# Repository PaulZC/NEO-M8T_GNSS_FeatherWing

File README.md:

# NEO-M8T GNSS FeatherWing

A clone of the [Adafruit Ultimate GPS FeatherWing](https://www.adafruit.com/product/3133) but with the u-blox NEO-M8T replacing the GlobalTop FGPMMOPA6H. The NEO-M8T can receive signals from GPS, Galileo and GLONASS or BeiDou concurrently and supports both SBAS and QZSS.
It also provides Multi-GNSS Raw Measurement (RAWX) Data which can be used for Post-Processed Kinematic (PPK) positioning.

**See [LEARN.md](https://github.com/PaulZC/NEO-M8T_GNSS_FeatherWing/blob/master/LEARN.md) for more details.**

[POST_PROCESS.md](https://github.com/PaulZC/NEO-M8T_GNSS_FeatherWing/blob/master/POST_PROCESS.md) contains results of a first time successful attempt at post-processed kinematic positioning using [rtkexplorer's demo5 version of RTKLIB](http://rtkexplorer.com/downloads/rtklib-code/).

See [NEO-M8T_GNSS_FeatherWing.pdf](https://github.com/PaulZC/NEO-M8T_GNSS_FeatherWing/blob/master/NEO-M8T_GNSS_FeatherWing.pdf) for the schematic, layout and Bill Of Materials.

The [Eagle](https://github.com/PaulZC/NEO-M8T_GNSS_FeatherWing/tree/master/Eagle) directory contains the schematic and pcb design files.

The [Arduino](https://github.com/PaulZC/NEO-M8T_GNSS_FeatherWing/tree/master/Arduino) directory contains code for the [Adafruit Feather M0 Adalogger](https://www.adafruit.com/products/2796) which will log RAWX data to SD card.

Distributed under a Creative Commons Attribution, Share-Alike license.

Enjoy!

**_Paul_**

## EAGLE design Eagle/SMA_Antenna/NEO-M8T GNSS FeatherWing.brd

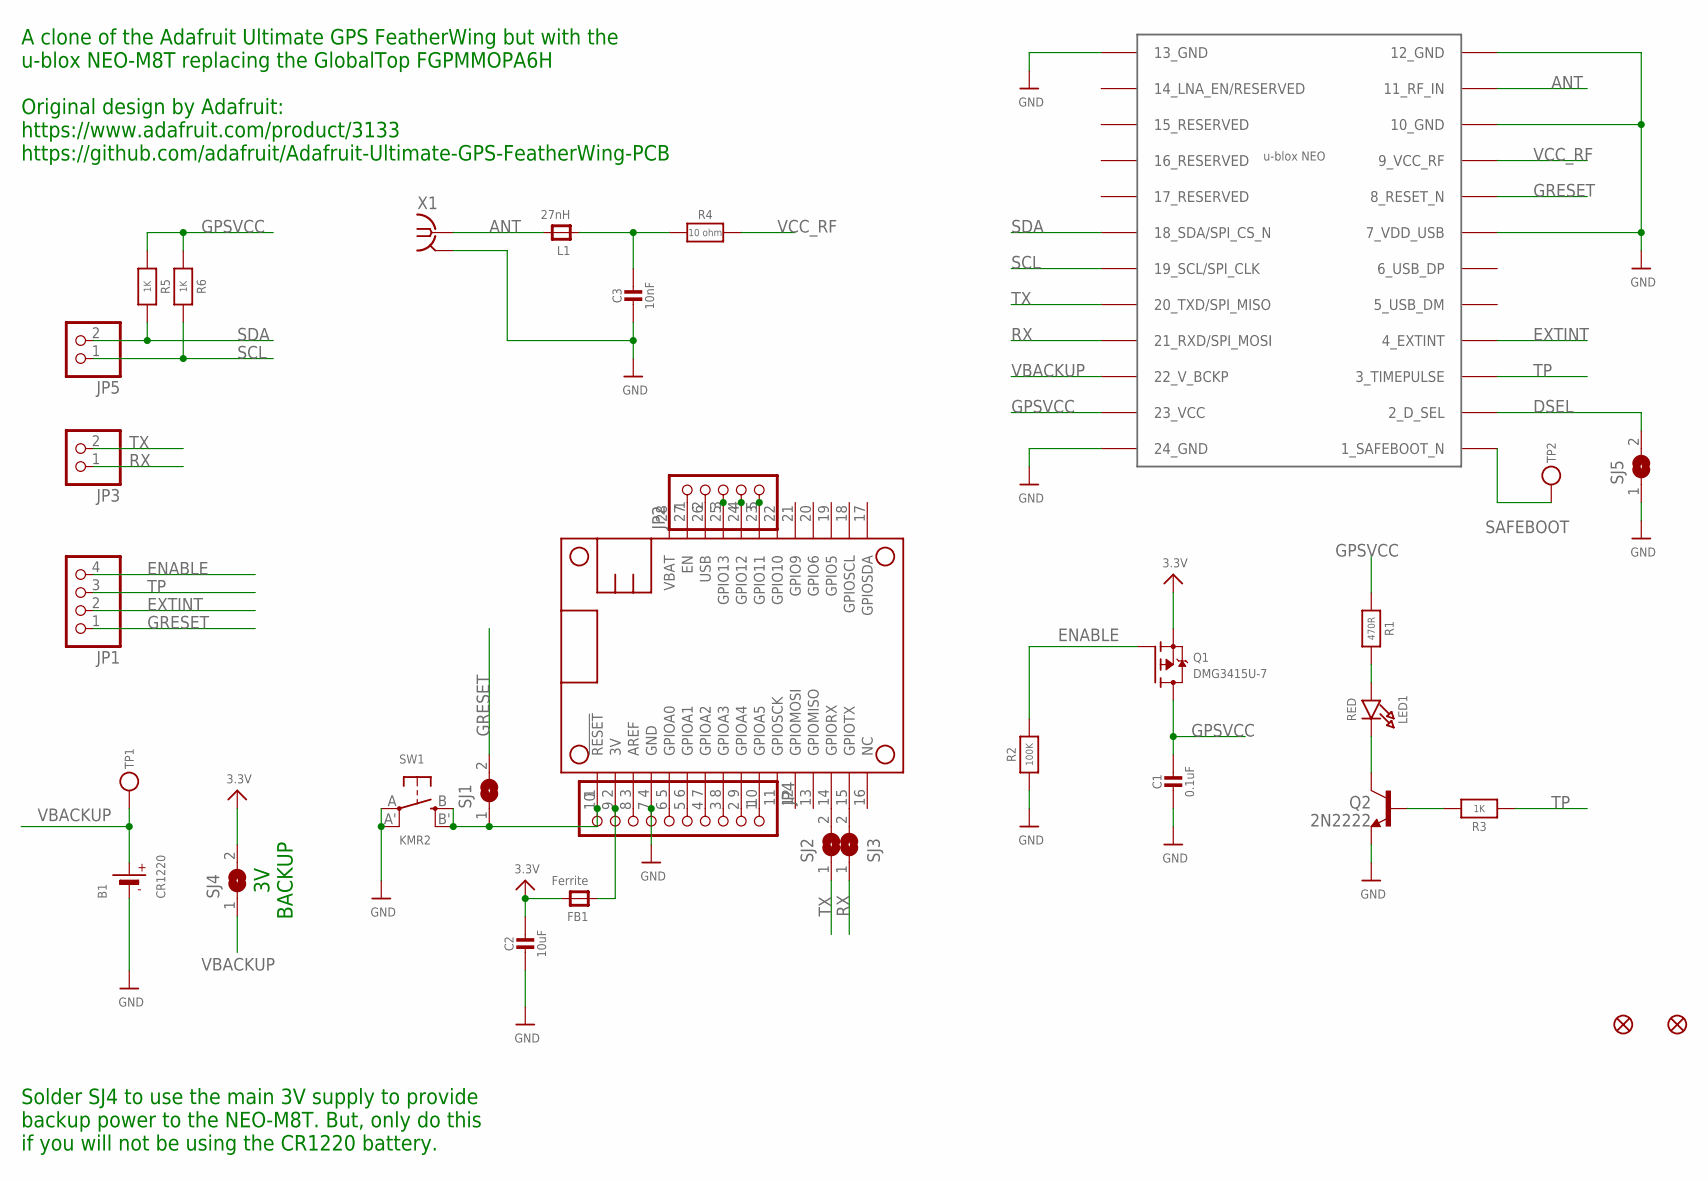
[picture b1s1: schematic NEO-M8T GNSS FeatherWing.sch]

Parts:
B1: CR1220; CR1220-2
C1: 0.1uF; 0805-NO
C2: 10uF; 0805-NO
C3: 10nF; 0805-NO
FB1: Ferrite; 0805-NO
FID1, FID2: FIDUCIAL""; FIDUCIAL_1MM
JP1: HEADER-1X4ROUND; 1X04_ROUND
JP2: HEADER-1X570MIL; 1X05_ROUND_70
JP3, JP5: HEADER-1X2ROUND; 1X02_ROUND
JP4: HEADER-1X10ROUND; 1X10_ROUND
L1: 27nH; 0805-NO
LED1: RED; CHIPLED_0805_NOOUTLINE
MS1: MICROBUILDER_FEATHERWINGSMA; MICROBUILDER_FEATHERWING_SMA
Q1: DMG3415U-7; SOT23-WIDE
Q2: 2N2222; SOT23-BEC
R1: 470R; 0603-NO
R2: 100K; 0805-NO
R3, R5, R6: 1K; 0603-NO
R4: 10 ohm; 0805-NO
SJ1, SJ4, SJ5: SOLDERJUMPER; SOLDERJUMPER_ARROW_NOPASTE
SJ2, SJ3: SOLDERJUMPERCLOSED; SOLDERJUMPER_CLOSEDWIRE
SW1: KMR2; BTN_KMR2_4.6X2.8
TP1, TP2: TESTPOINTROUND1.5MM; TESTPOINT_ROUND_1.5MM
U1: NEO-M8
X1: SMA-142-0711-821/826; J502-ND-142-0711-821/826

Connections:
3.3V: C2.1, FB1.2, Q1.2 (S), SJ4.2
3V: FB1.1, JP4.9, MS1.2 (3V)
ANT: L1.2, U1.11 (11_RF_IN), X1.1
DSEL: SJ5.2, U1.2 (2_D_SEL)
ENABLE: JP1.4, Q1.1 (G), R2.2
EXTINT: JP1.2, U1.4 (4_EXTINT)
GND: B1.-, C1.2, C2.2, C3.2, JP4.7, MS1.4 (GND), Q2.E, R2.1, SJ5.1, SW1.A, SW1.A' (P1), U1.7 (7_VDD_USB), U1.10 (10_GND), U1.12 (12_GND), U1.13 (13_GND), U1.24 (24_GND), X1.G@1 (2), X1.G@2 (2), X1.G@3 (2), X1.G@4 (2)
GPSVCC: C1.1, Q1.3 (D), R1.1, R5.1, R6.1, U1.23 (23_VCC)
GRESET: JP1.1, SJ1.2, U1.8 (8_RESET_N)
unnamed: JP2.3, MS1.25 (GPIO13)
unnamed: LED1.A, R1.2
unnamed: JP2.4, MS1.24 (GPIO12)
unnamed: C3.1, L1.1, R4.1
unnamed: JP2.5, MS1.23 (GPIO11)
unnamed: JP4.1, MS1.10 (GPIOA5)
unnamed: JP4.2, MS1.9 (GPIOA4)
unnamed: JP4.3, MS1.8 (GPIOA3)
unnamed: JP4.4, MS1.7 (GPIOA2)
unnamed: JP4.5, MS1.6 (GPIOA1)
unnamed: JP4.6, MS1.5 (GPIOA0)
unnamed: JP4.8, MS1.3 (AREF)
unnamed: JP2.1, MS1.27 (EN)
unnamed: MS1.14 (GPIORX), SJ2.2
unnamed: MS1.15 (GPIOTX), SJ3.2
unnamed: LED1.C, Q2.C
unnamed: Q2.B, R3.2
RST: JP4.10, MS1.1 (!RESET), SJ1.1, SW1.B (S), SW1.B' (S1)
RX: JP3.1, SJ3.1, U1.21 (21_RXD/SPI_MOSI)
SAFEBOOT: TP2.P$1, U1.1 (1_SAFEBOOT_N)
SCL: JP5.1, R6.2, U1.19 (19_SCL/SPI_CLK)
SDA: JP5.2, R5.2, U1.18 (18_SDA/SPI_CS_N)
TP: JP1.3, R3.1, U1.3 (3_TIMEPULSE)
TX: JP3.2, SJ2.1, U1.20 (20_TXD/SPI_MISO)
USB: JP2.2, MS1.26 (USB)
VBACKUP: B1.+, SJ4.1, TP1.P$1, U1.22 (22_V_BCKP)
VCC_RF: R4.2, U1.9 (9_VCC_RF)

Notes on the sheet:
A clone of the Adafruit Ultimate GPS FeatherWing but with the u-blox NEO-M8T replacing the GlobalTop FGPMMOPA6H Original design by Adafruit: https://www.adafruit.com/product/3133 https://github.com/adafruit/Adafruit-Ultimate-GPS-FeatherWing-PCB
3V BACKUP
Solder SJ4 to use the main 3V supply to provide backup power to the NEO-M8T. But, only do this if you will not be using the CR1220 battery.

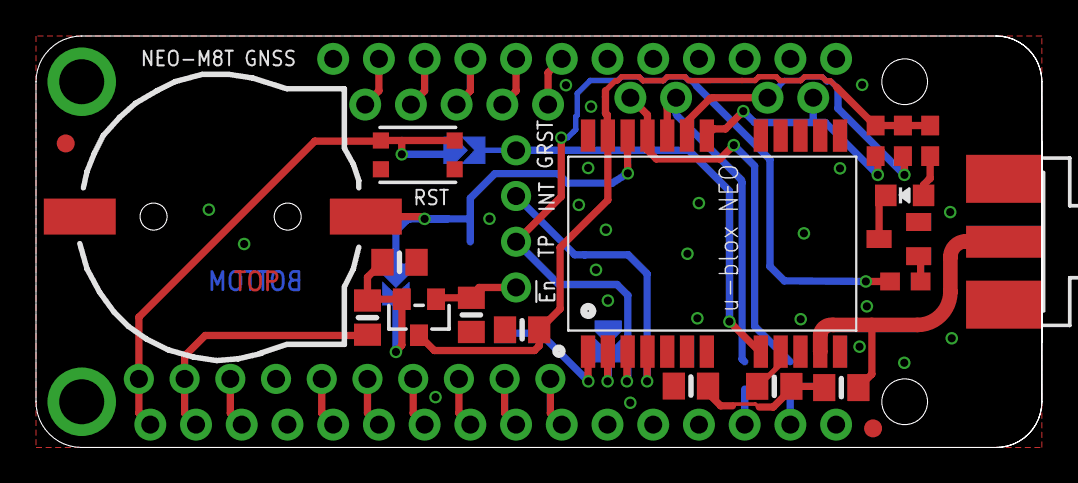
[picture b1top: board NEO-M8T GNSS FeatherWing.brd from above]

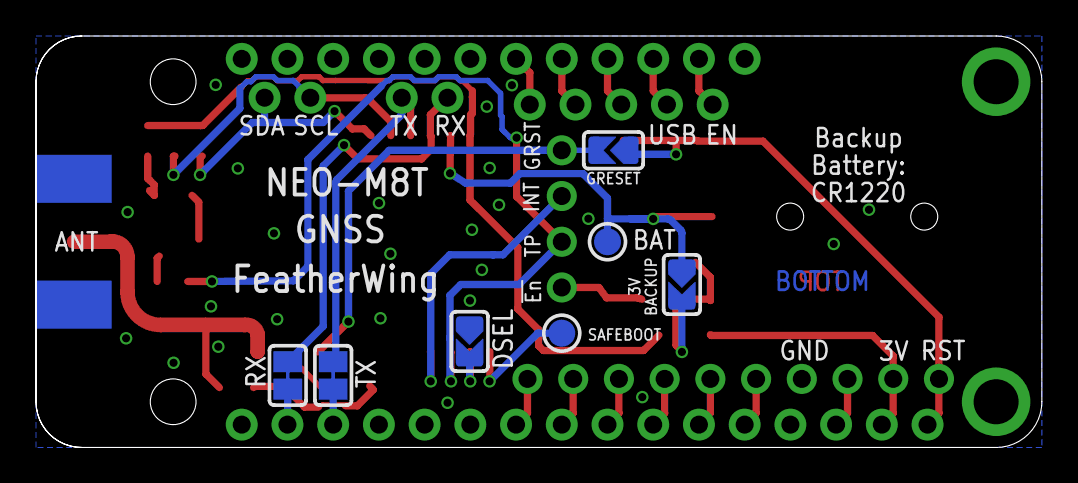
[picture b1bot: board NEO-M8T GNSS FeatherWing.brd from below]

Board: 2 copper layers, 55.9 x 22.9 mm, 33 parts (7 on the bottom side), 36 nets.

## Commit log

2017-08-13 :lollipop: Added .gitattributes & .gitignore files
2017-08-14 Initial commit
    Initial commit. PCB is just about ready for testing. Photos and Arduino
    code to follow.
2017-08-14 Updated the README
2017-08-14 Added initial Arduino and Python code
2017-08-14 Groundplane improvements
2017-08-16 Added SCL and SDA pullups
    Managed to squeeze in pull-up resistors for SCL and SDA.
2017-08-16 Added images of the PCB
2017-08-17 Added the BOM
2017-08-17 Minor tweaks
2017-08-19 Draft RAWX_Logger Arduino code added
2017-08-20 Added extra debug messages
2017-09-09 Substantial update after first successful PCB tests
2017-09-09 Updated the image links
2017-09-09 Resized the images
2017-09-10 Fixed the buffer overrun!
2017-09-10 Added Adalogger photos
2017-09-10 Added an image of the SAFEBOOT pad
2017-09-10 Added a close-up of the stop switch
2017-09-10 Added three cross-references
2017-09-14 Added image of EN switch
2017-09-14 Updated the image of the EN switch
2017-09-17 Now logs RAWX, SFRBX and TM2 messages
    Updated the Arduino and Python code so that they log RXM-RAWX, RXM-SFRBX
    and TIM-TM2 messages, not just RXM-RAWX.
2017-09-17 Added POST_PROCESS.md and images
2017-09-17 Updated POST_PROCESS.md
2017-09-19 Updated NEO-M8T_GNSS_RAWX_Logger.py
    Updated NEO-M8T_GNSS_RAWX_Logger.py. Code now creates a 'clean' log
    file: the final received packet(s) are logged to file correctly.
2017-09-19 Updated UBX_Checker.py
    Updated UBX_Checker.py. Code now counts how many of each message type
    are received.
2017-09-19 Updated RAWX_Logger: added sendUBX.
    Updated RAWX_Logger. Added sendUBX which calculates the UBX checksums
    for you. Now defaults to GPS + Galileo + GLONASS + SBAS.
2017-09-19 Updated the .brd. Now uses smaller vias.
    Updated the .brd. Now uses smaller vias which will be covered with
    solder resist.
2017-09-19 Updated LEARN.md.
2017-09-20 Excluded the vias from the stop layers
2017-09-24 Added least squares fit data
2017-09-24 Updated README.md and LEARN.md
2017-09-30 Updated circle fitting
2017-10-01 Added a histogram of the positional error
2017-11-10 Added extra screenshots
2017-11-26 Corrected references to PPK
2018-02-13 Added RAWX_Logger_2
    RAWX_Logger_2 saves base (static) data into files called b_hhmmss.ubx
    and rover data into files called r_hhmmss.ubx.
    A new log file is automatically opened every INTERVAL minutes.
2018-02-16 Updated both RAWX_Loggers. Improved reliability.
2018-03-06 RAWX_Logger .ubx files now have correct dates and times
2018-03-06 Updates and a bugfix
    The .ubx log files now have the correct date and time for creation and
    last update. Fixed a rookie error in the RTC ISR - moved the
    next-alarm-time code into the main loop as this was causing occasional
    serial data loss during file changes.
2018-03-08 Added RAWX_Logger_3
2018-03-10 Updated RAWX_Logger_3: now handles loss of sync.
2018-03-20 Added the PCB design for the SMA antenna.
2018-03-20 Added the PCB design for an SMA antenna.
2018-03-20 Updated the RTKPOST options
2018-10-01 Added RTC library for M0
2018-10-01 Updated LEARN.md
2019-11-18 Added RAWX_Logger_4
